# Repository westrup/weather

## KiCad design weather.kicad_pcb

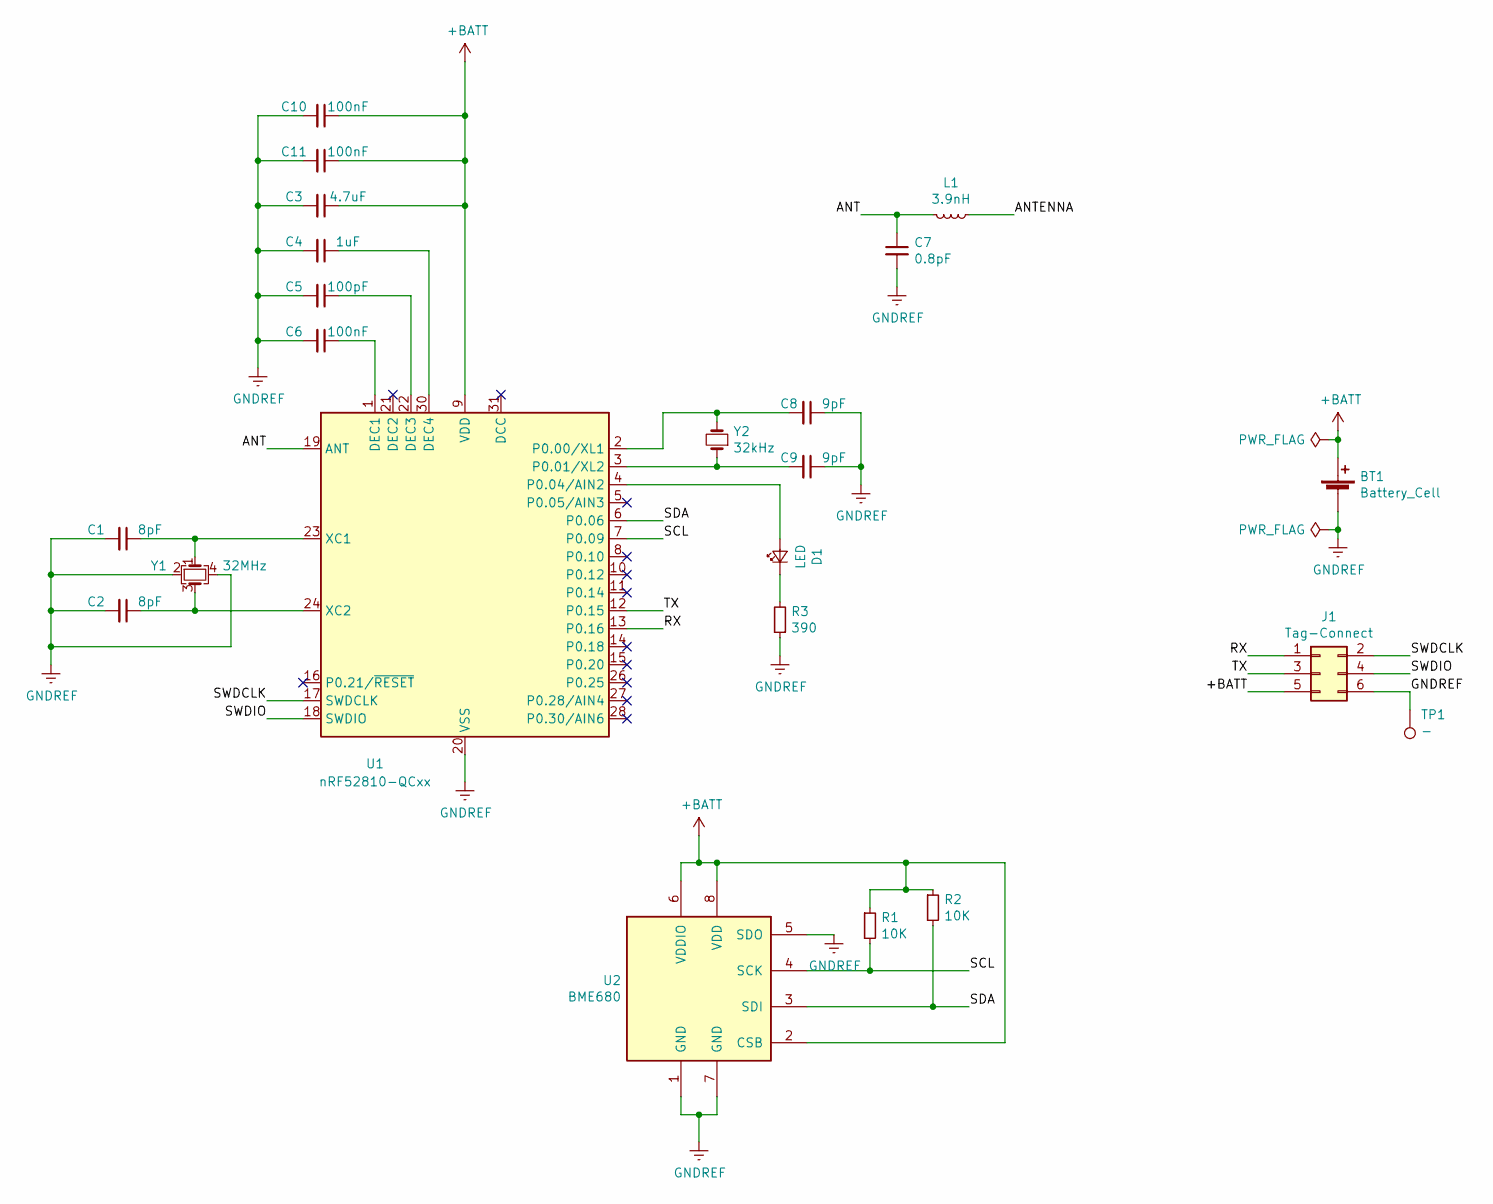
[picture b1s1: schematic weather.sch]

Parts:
BT1: Battery_Cell; BatteryHolder_Linx_001_THM
C1, C2: 8pF; C_0603_1608Metric
C3: 4.7uF; C_0603_1608Metric
C4: 1uF; C_0603_1608Metric
C5: 100pF; C_0603_1608Metric
C6, C10, C11: 100nF; C_0603_1608Metric
C7: 0.8pF; C_0603_1608Metric
C8, C9: 9pF; C_0603_1608Metric
D1: LED; LED_0603_1608Metric
J1: Tag-Connect; Tag-Connect_TC2030-IDC-NL_2x03_P1.27mm_Vertical
L1: 3.9nH; L_0603_1608Metric
R1, R2: 10K; R_0603_1608Metric
R3: 390; R_0603_1608Metric
TP1: -; TestPoint_THTPad_D2.0mm_Drill1.0mm
U1: nRF52810-QCxx; QFN-32-1EP_5x5mm_P0.5mm_EP3.6x3.6mm
U2: BME680; Bosch_LGA-8_3x3mm_P0.8mm_ClockwisePinNumbering
Y1: 32MHz; Crystal_SMD_3225-4Pin_3.2x2.5mm
Y2: 32kHz; Crystal_SMD_3215-2Pin_3.2x1.5mm

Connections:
+BATT: BT1.1 (+), C3.1, C10.1, C11.1, J1.5, R1.1, R2.1, U1.9 (VDD), U1.25 (VDD), U1.32 (VDD), U2.2 (CSB), U2.6 (VDDIO), U2.8 (VDD)
/ANT: C7.1, L1.2, U1.19 (ANT)
/ANTENNA: L1.1
/RX: J1.1, U1.13 (P0.16)
/SCL: R1.2, U1.7 (P0.09), U2.4 (SCK)
/SDA: R2.2, U1.6 (P0.06), U2.3 (SDI)
/SWDCLK: J1.2, U1.17 (SWDCLK)
/SWDIO: J1.4, U1.18 (SWDIO)
/TX: J1.3, U1.12 (P0.15)
GNDREF: BT1.2 (-), C1.2, C2.2, C3.2, C4.2, C5.2, C6.2, C7.2, C8.1, C9.1, C10.2, C11.2, J1.6, R3.1, TP1.1, U1.20 (VSS), U1.29 (VSS), U1.33 (VSS), U2.1 (GND), U2.5 (SDO), U2.7 (GND), Y1.2, Y1.4
unnamed: C1.1, U1.23 (XC1), Y1.1
unnamed: C2.1, U1.24 (XC2), Y1.3
unnamed: C4.1, U1.30 (DEC4)
unnamed: C5.1, U1.22 (DEC3)
unnamed: C6.1, U1.1 (DEC1)
unnamed: C8.2, U1.2 (P0.00/XL1), Y2.2
unnamed: C9.2, U1.3 (P0.01/XL2), Y2.1
unnamed: D1.1 (K), R3.2
unnamed: D1.2 (A), U1.4 (P0.04/AIN2)

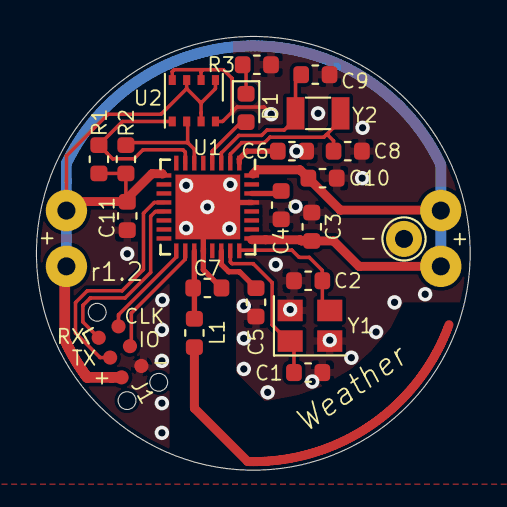
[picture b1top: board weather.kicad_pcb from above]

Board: 2 copper layers, 24.1 x 24.1 mm, 23 parts (1 on the bottom side), 18 nets.

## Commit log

2018-09-10 Weather sensor
2018-09-10 rm fp-info-cache
2018-09-11 Move LED to analog pin
2018-09-24 nRF5_SDK_15.2.0_9412b96
2018-09-26 Modified beacon example
    Beacon
    Blink
    Sensor read
2018-09-26 Advertise temperature and humidity
2018-09-26 openocd, gdb, makefile
2018-09-26 Config sensor 1Hz
2018-09-28 HDC2080 DRDY / INT pin, and move LED pin
2018-10-09 Timer fixes
2018-10-09 Cleanup
2019-04-01 KiCad upgrade
2019-04-01 Switch to BME680 sensor
2020-03-08 `vallen` is verified to be less than `len`, therefore, it can never be the case that `vallen >= len + sizeof(rhostname)`.
    This PR fixes the check so the `rhostname` array does not overflow.
    Reported-by: Github Security Lab <securitylab@github.com>
